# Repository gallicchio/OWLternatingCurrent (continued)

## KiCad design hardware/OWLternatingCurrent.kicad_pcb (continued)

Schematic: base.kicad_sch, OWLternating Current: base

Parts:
AE1: moon; TestPoint_Pad_D1.5mm
AE2: ghost; TestPoint_Pad_D1.5mm
C1: 470u 35V; CP_Elec_10x12.6; MPN MA35V470M10X13; LCSC C46550472
C2, C3, C32, C49, C54, C59, C64, C69, C74: 10u 25V; C_0805_2012Metric; MPN CL21A106KAYNNNE; LCSC C15850
C4, C5, C35, C37, C40, C42, C43, C45, C47, C48, C52, C53, C57, C58, C62, C63, C66, C68, C70, C71, C73, C75: 100n; C_0603_1608Metric; MPN CC0603KRX7R9BB104; LCSC C14663
C6, C7: 22u 25V; C_0805_2012Metric; MPN CL21A226MAQNNNE; LCSC C45783
C8, C9: 1u; C_0402_1005Metric; MPN CL05A105KA5NQNC; LCSC C52923
C10: 4.7u; C_0402_RPi; MPN CL05A475MP5NRNC; LCSC C23733
C11, C12: 4.7u; C_0402_RPi_wide; MPN CL05A475MP5NRNC; LCSC C23733
C13, C14, C15, C16, C17, C18, C19, C20, C21, C22, C23, C24: 100n; C_0402_1005Metric; MPN CL05B104KO5NNNC; LCSC C1525
C25: 10u; C_0603_1608Metric; MPN CL10A106KP8NNNC; LCSC C19702
C26, C27: 15p; C_0402_1005Metric; MPN 0402CG150J500NT; LCSC C1548
C28, C31, C46, C51, C56, C61: 22n; C_0603_1608Metric; MPN CL10B223KB8NNNC; LCSC C21122
C29, C30, C50, C55, C60, C65: 10n; C_0603_1608Metric; MPN 0603B103K500NT; LCSC C57112
C33, C34, C39, C41, C44, C67, C72: 1u; C_0603_1608Metric; MPN CL10A105KB8NNNC; LCSC C15849
C36, C38: 15p; C_0603_1608Metric; MPN CL10C150JB8NNNC; LCSC C1644
D1: BZT52C10; D_SOD-123; MPN BZT52C10; LCSC C173431
D2: SMBJ15A; D_SMB; MPN SMBJ15A; LCSC C19077569
D3, D4: B5819W; D_SOD-123; MPN B5819W SL; LCSC C8598
D5, D6: ESD 0.9pF; D_SOD-923; MPN ESD9L5.0ST5G; LCSC C82326
D7, D8, D32: orange x3; LED_RGB_5050-6; MPN HL-AF-5060S22OC-3-S1-THL; LCSC C516304
D9, D10, D11, D12, D14, D18, D28, D30, D31, D33, D34, D35: purple; LED_0603_1608Metric; MPN GL0603PU01; LCSC C51933300
D13, D15, D16, D17, D19, D20, D21, D22, D23, D24, D25, D26, D27, D29, D36, D37: violet; LED_Everlight-SMD3528_3.5x2.8mm_67-21ST; MPN HL-A-3528S7VC-S1-13HL; LCSC C516136
F1: 3A PTC; Fuse_2920_7451Metric; MPN BSMD2920-300-24V; LCSC C2977527
H1, H2, H3, H4: foot; MountingHole_3.2mm_M3
J1: 12V DC; BarrelJack_XKB_DC-005-5A-2.0_Horizontal; MPN DC-005-5A-2.0; LCSC C381116
J2: USB-C; USB_C_Receptacle_HRO_TYPE-C-31-M-12; MPN TYPE-C-31-M-12; LCSC C165948
J3: TREE; PinSocket_2x08_P2.54mm_Vertical; MPN PM254-2-08-Z-8.5; LCSC C2897409
J4: SWD; JST_SH_BM03B-SRSS-TB_1x03-1MP_P1.00mm_Vertical; MPN BM03B-SRSS-TB(LF)(SN); LCSC C160389
J5: UART; JST_SH_BM03B-SRSS-TB_1x03-1MP_P1.00mm_Vertical; MPN BM03B-SRSS-TB(LF)(SN); LCSC C160389
L1: 10uH; L_Changjiang_FXL0630; MPN FXL0630-100-M; LCSC C167223
L2: 3.3uH; L_Abracon_AOTA-B201610_RPi; MPN AOTA-B201610S3R3-101-T; LCSC C42411119
L3, L4, L5: 33uH coil; Coil_PEND; MPN PCB coil
L6, L7: 30uH coil; Coil_PERCH; MPN PCB coil
LS1: 8R 1W; Speaker_GSPK2307P_D23mm_P10mm; MPN GSPK2307P-8R1W; LCSC C530531
Q1: AO4407A; SOIC-8_3.9x4.9mm_P1.27mm; MPN AO4407A; LCSC C2841482
R1, R2, R22, R25, R28, R47, R52, R56: 100k; R_0603_1608Metric; MPN 0603WAF1003T5E; LCSC C25803
R3, R48: 22k; R_0603_1608Metric; MPN 0603WAF2202T5E; LCSC C31850
R4: 36k; R_0603_1608Metric; MPN 0603WAF3602T5E; LCSC C23147
R5: 5.1k; R_0603_1608Metric; MPN 0603WAF5101T5E; LCSC C23186
R6: 33; R_0402_RPi; MPN 0402WGF330JTCE; LCSC C25105
R7, R8: 27; R_0402_1005Metric; MPN RC0402FR-0727RL; LCSC C138021
R9, R10: 5.1k; R_0402_1005Metric; MPN 0402WGF5101TCE; LCSC C25905
R11, R14: 1k; R_0402_1005Metric; MPN 0402WGF1001TCE; LCSC C11702
R12, R13, R15, R16: 100; R_0402_1005Metric; MPN 0402WGF1000TCE; LCSC C25076
R17, R18, R19, R26, R29, R36, R38, R40, R42, R53, R57: 1k; R_0603_1608Metric; MPN 0603WAF1001T5E; LCSC C21190
R20, R21: 220k; R_0603_1608Metric; MPN 0603WAF2203T5E; LCSC C22961
R23, R34, R43, R44, R45, R46, R51, R55: 10k; R_0603_1608Metric; MPN 0603WAF1002T5E; LCSC C25804
R24, R27: 33; R_0603_1608Metric; MPN 0603WAF330JT5E; LCSC C23140
R30, R31, R35, R37, R39, R41: 2.2k; R_0603_1608Metric; MPN 0603WAF2201T5E; LCSC C4190
R32: 3.3k; R_0603_1608Metric; MPN 0603WAF3301T5E; LCSC C22978
R33, R49: 4.7k; R_0603_1608Metric; MPN 0603WAF4701T5E; LCSC C23162
R50, R54: 0.1; R_1206_3216Metric; MPN 1206W4F100LT5E; LCSC C25334
SW1: BOOT; SW_SPST_TS-1088-xR020; MPN TS-1088-AR02016; LCSC C720477
SW2: SPELL; SW_SPST_TS-1088-xR020; MPN TS-1088-AR02016; LCSC C720477
SW3: SOUND; SW_SPDT_Shouhan_MSK12C02; MPN MSK12C02; LCSC C431540
TP1: +12V; TestPoint_Pad_D1.5mm
TP2: +4.8V; TestPoint_Pad_D1.5mm
TP3: +3V3; TestPoint_Pad_D1.0mm
TP4: VSYS; TestPoint_Pad_D1.0mm
TP5: +1V1; TestPoint_Pad_D1.0mm
TP6: VBUS; TestPoint_Pad_D1.0mm
U1: TPS54302; SOT-23-6; MPN TPS54302DDCR; LCSC C311983
U2: XC6206 3.3V; SOT-23; MPN XC6206P332MR-G; LCSC C5446
U3: LP5036; VQFN-46-1EP_5x6mm_P0.4mm_EP2.8x3.8mm; MPN LP5036RJVR; LCSC C701961
U4: RP2354A; RP2350A_QFN-60_7x7mm_P0.4mm_RPi; MPN RP2354A; LCSC C41378174
U5, U6, U7, U8: DRV8874; HTSSOP-16-1EP_4.4x5mm_P0.65mm_EP3.55x2.46mm_TI_PWP0016J; MPN DRV8874PWPR; LCSC C1855818
U9, U10: UCC27524; SOIC-8_3.9x4.9mm_P1.27mm; MPN UCC27524DR; LCSC C465729
U11: 74HC4051; TSSOP-16_4.4x5mm_P0.65mm; MPN 74HC4051PW,118; LCSC C5645
U12, U13: 74LVC1G14; SOT-23-5; MPN SN74LVC1G14DBVR; LCSC C7835
U14: NS4150B; MSOP-8_3x3mm_P0.65mm; MPN NS4150B; LCSC C189961
U15: LSM6DS3TR-C; Bosch_LGA-14_3x2.5mm_P0.5mm; MPN LSM6DS3TR-C; LCSC C967633
U16: LTR-303ALS; Lite-On_LTR-303ALS-01; MPN LTR-303ALS-01; LCSC C364577
U17: TMAG5273A2; SOT-23-6; MPN TMAG5273A2QDBVR; LCSC C3715882
U18: OPA2333; SOIC-8_3.9x4.9mm_P1.27mm; MPN OPA2333AIDR; LCSC C38732
Y1: 12MHz; Crystal_SMD_3225-4Pin_3.2x2.5mm; MPN ABM8-272-T3; LCSC C20625731

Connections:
+1V1: C12.1, C13.1, C14.1, C15.1, L2.1, TP5.1, U4.6 (DVDD), U4.23 (DVDD), U4.39 (DVDD), U4.50 (VREG_FB)
+3V3: C9.1, C11.1, C16.1, C17.1, C18.1, C19.1, C20.1, C21.1, C22.1, C23.1, C24.1, C35.1, C37.1, C39.1, C40.1, C42.1, C43.1, C44.1, C45.1, C66.1, C71.1, J3.2, R6.1, R30.1, R31.1, R34.1, TP3.1, U2.2 (VO), U3.40 (VCC), U3.43 (EN), U4.1 (IOVDD), U4.11 (IOVDD), U4.20 (IOVDD), U4.30 (IOVDD), U4.38 (IOVDD), U4.44 (ADC_AVDD), U4.45 (IOVDD), U4.49 (VREG_VIN), U4.53 (USB_OTP_VDD), U4.54 (QSPI_IOVDD), U5.5 (VREF), U5.16 (PMODE), U6.5 (VREF), U6.16 (PMODE), U7.5 (VREF), U7.16 (PMODE), U8.5 (VREF), U8.16 (PMODE), U11.16 (VCC), U12.5 (VCC), U13.5 (VCC), U15.5 (VDDIO), U15.8 (VDD), U15.12 (CS), U16.1 (VDD), U17.4 (VCC), U18.8 (V+)
+5V: C6.1, C7.1, C32.1, C33.1, C67.1, C68.1, C72.1, C73.1, D3.2 (A), D7.1 (A), D7.2 (A), D7.3 (A), D8.1 (A), D8.2 (A), D8.3 (A), D9.2 (A), D10.2 (A), D11.2 (A), D12.2 (A), D13.2 (A), D14.2 (A), D15.2 (A), D16.2 (A), D17.2 (A), D18.2 (A), D19.2 (A), D20.2 (A), D21.2 (A), D22.2 (A), D23.2 (A), D24.2 (A), D25.2 (A), D26.2 (A), D27.2 (A), D28.2 (A), D29.2 (A), D30.2 (A), D31.2 (A), D32.1 (A), D32.2 (A), D32.3 (A), D33.2 (A), D34.2 (A), D35.2 (A), D36.2 (A), D37.2 (A), J3.4, L1.2, R4.1, R45.1, SW3.1 (A), TP2.1, U9.6 (VDD), U10.6 (VDD), U14.6 (VCC)
+12V: C1.1, C2.1, C3.1, C4.1, C47.2, C48.1, C49.1, C52.2, C53.1, C54.1, C57.2, C58.1, C59.1, C62.2, C63.1, C64.1, D1.1 (K), D2.1 (K), Q1.1 (S), Q1.2 (S), Q1.3 (S), R2.1, R47.1, TP1.1, U1.3 (VIN), U5.11 (VM), U6.11 (VM), U7.11 (VM), U8.11 (VM)
/Base/AUDIO: R18.2, U4.12 (GPIO8)
/Base/BUTTON: R17.2, U4.29 (GPIO18)
/Base/CATRING0: D34.1 (K), U3.33 (OUT32)
/Base/CATRING1: D35.1 (K), U3.34 (OUT33)
/Base/CATRING2: D28.1 (K), U3.27 (OUT26)
/Base/CAT_A: C74.1, U10.7 (OUTA)
/Base/CAT_B: L7.2, U10.5 (OUTB)
/Base/CAT_C: C74.2, L7.1
/Base/DRV_nFAULT: R34.2, U4.34 (GPIO22), U5.4 (~FAULT), U6.4 (~FAULT), U7.4 (~FAULT), U8.4 (~FAULT)
/Base/DRV_nSLEEP: R33.1, U4.31 (GPIO19), U5.3 (~SLEEP), U6.3 (~SLEEP), U7.3 (~SLEEP), U8.3 (~SLEEP)
/Base/FAM1_A: U4.7 (GPIO4), U9.2 (INA)
/Base/FAM1_B: U4.8 (GPIO5), U9.4 (INB)
/Base/FAM1_IAVG: C70.1, R51.2, U18.3 (+)
/Base/FAM1_ISENSE: R52.2, U11.13 (A0), U18.1
/Base/FAM2_A: U4.18 (GPIO14), U10.2 (INA)
/Base/FAM2_B: U4.19 (GPIO15), U10.4 (INB)
/Base/FAM2_IAVG: C75.1, R55.2, U18.5 (+)
/Base/FAM2_ISENSE: R56.2, U11.12 (A3), U18.7
/Base/FAM_EN: R49.1, U4.35 (GPIO23), U9.1 (ENA), U9.8 (ENB), U10.1 (ENA), U10.8 (ENB)
/Base/GHOST: AE2.1, D6.1 (K), R29.1
/Base/HALL: J3.1, U4.41 (GPIO27/ADC1)
/Base/IMU_INT: U4.3 (GPIO1), U15.4 (INT1)
/Base/LEV_A: J3.14, J3.16, U8.8 (OUT1)
/Base/LEV_B: J3.8, J3.10, U8.10 (OUT2)
/Base/LEV_IN1: U4.16 (GPIO12), U8.1 (IN1)
/Base/LEV_IN2: U4.17 (GPIO13), U8.2 (IN2)
/Base/LEV_IPROPI: C50.1, R36.2, U4.42 (GPIO28/ADC2)
/Base/MOON: AE1.1, D5.1 (K), R26.1
/Base/MUX_OUT: U4.43 (GPIO29/ADC3), U11.3 (A)
/Base/MUX_S0: U4.36 (GPIO24), U11.11 (S0)
/Base/MUX_S1: U4.37 (GPIO25), U11.10 (S1)
/Base/MUX_S2: U4.40 (GPIO26/ADC0), U11.9 (S2)
/Base/OWLRING0: D12.1 (K), U3.6 (OUT5)
/Base/OWLRING1: D18.1 (K), U3.12 (OUT11)
/Base/OWLRING2: D14.1 (K), U3.8 (OUT7)
/Base/OWL_A: C69.1, U9.7 (OUTA)
/Base/OWL_B: L6.2, U9.5 (OUTB)
/Base/OWL_C: C69.2, L6.1
/Base/PEND1_A: L3.1, U5.8 (OUT1)
/Base/PEND1_B: L3.2, U5.10 (OUT2)
/Base/PEND1_IN1: U4.9 (GPIO6), U5.1 (IN1)
/Base/PEND1_IN2: U4.10 (GPIO7), U5.2 (IN2)
/Base/PEND1_IPROPI: C55.1, R38.2, U11.4 (A7)
/Base/PEND2_A: L4.1, U6.8 (OUT1)
/Base/PEND2_B: L4.2, U6.10 (OUT2)
/Base/PEND2_IN1: U4.4 (GPIO2), U6.1 (IN1)
/Base/PEND2_IN2: U4.5 (GPIO3), U6.2 (IN2)
/Base/PEND2_IPROPI: C60.1, R40.2, U11.5 (A5)
/Base/PEND3_A: L5.1, U7.8 (OUT1)
/Base/PEND3_B: L5.2, U7.10 (OUT2)
/Base/PEND3_IN1: U4.14 (GPIO10), U7.1 (IN1)
/Base/PEND3_IN2: U4.15 (GPIO11), U7.2 (IN2)
/Base/PEND3_IPROPI: C65.1, R42.2, U11.15 (A2)
/Base/PUMPKIN0: D8.4 (K), D8.5 (K), D8.6 (K), U3.2 (OUT1)
/Base/PUMPKIN1: D7.4 (K), D7.5 (K), D7.6 (K), U3.1 (OUT0)
/Base/PUMPKIN2: D32.4 (K), D32.5 (K), D32.6 (K), U3.31 (OUT30)
/Base/QSPI_SS: R14.2, U4.60 (~QSPI_SS)
/Base/SCL: J3.5, R30.2, U3.42 (SCL), U4.33 (GPIO21), U15.13 (SCL), U16.4 (SCL), U17.1 (SCL)
/Base/SDA: J3.3, R31.2, U3.41 (SDA), U4.32 (GPIO20), U15.14 (SDA), U16.6 (SDA), U17.6 (SDA)
/Base/STAR0: D17.1 (K), U3.11 (OUT10)
/Base/STAR1: D16.1 (K), U3.10 (OUT9)
/Base/STAR2: D15.1 (K), U3.9 (OUT8)
/Base/STAR3: D13.1 (K), U3.7 (OUT6)
/Base/STAR4: D37.1 (K), U3.36 (OUT35)
/Base/STAR5: D36.1 (K), U3.35 (OUT34)
/Base/STAR6: D29.1 (K), U3.28 (OUT27)
/Base/STAR7: D24.1 (K), U3.23 (OUT22)
/Base/STAR8: D23.1 (K), U3.22 (OUT21)
/Base/STAR9: D25.1 (K), U3.24 (OUT23)
/Base/STAR10: D26.1 (K), U3.25 (OUT24)
/Base/STAR11: D27.1 (K), U3.26 (OUT25)
/Base/STARX0: D20.1 (K), U3.14 (OUT13)
/Base/STARX1: D21.1 (K), U3.20 (OUT19)
/Base/STARX2: D19.1 (K), U3.13 (OUT12)
/Base/STARX3: D22.1 (K), U3.21 (OUT20)
/Base/SWCLK: R12.2, U4.24 (SWCLK)
/Base/SWDIO: R13.2, U4.25 (SWDIO)
/Base/THEREMIN_PITCH: R24.2, U4.2 (GPIO0)
/Base/THEREMIN_VOL: R27.2, U4.13 (GPIO9)
/Base/UART_RX: R15.2, U4.28 (GPIO17)
/Base/UART_TX: R16.2, U4.27 (GPIO16)
/Base/USB_D+: J2.A6 (D+), J2.B6 (D+), R8.1
/Base/USB_D-: J2.A7 (D-), J2.B7 (D-), R7.1
/Base/USB_DM: R7.2, U4.51 (USB_DM)
/Base/USB_DP: R8.2, U4.52 (USB_DP)
/Base/V5_SENSE: R45.2, R46.1, U11.1 (A4)
/Base/V12_SENSE: R47.2, R48.1, U11.2 (A6)
/Base/VBUS_SENSE: R43.2, R44.1, U11.14 (A1)
/Base/WISP0: D10.1 (K), U3.4 (OUT3)
/Base/WISP1: D9.1 (K), U3.3 (OUT2)
/Base/WISP2: D11.1 (K), U3.5 (OUT4)
/Base/WISP3: D33.1 (K), U3.32 (OUT31)
/Base/WISP4: D31.1 (K), U3.30 (OUT29)
/Base/WISP5: D30.1 (K), U3.29 (OUT28)
/Base/XIN: C26.2, U4.21 (XIN), Y1.1
/Base/XOUT: R11.2, U4.22 (XOUT)
GND: C1.2, C2.2, C3.2, C4.2, C6.2, C7.2, C8.2, C9.2, C10.2, C11.2, C12.2, C13.2, C14.2, C15.2, C16.2, C17.2, C18.2, C19.2, C20.2, C21.2, C22.2, C23.2, C24.2, C25.2, C26.1, C27.1, C29.2, C30.2, C31.2, C32.2, C33.2, C34.2, C35.2, C36.2, C37.2, C38.2, C39.2, C40.2, C41.2, C42.2, C43.2, C44.2, C45.2, C48.2, C49.2, C50.2, C53.2, C54.2, C55.2, C58.2, C59.2, C60.2, C63.2, C64.2, C65.2, C66.2, C67.2, C68.2, C70.2, C71.2, C72.2, C73.2, C75.2, D2.2 (A), D5.2 (A), D6.2 (A), J1.2, J1.3, J2.A1 (GND), J2.A12 (GND), J2.B1 (GND), J2.B12 (GND), J2.SH (SHIELD), J3.6, J3.7, J3.9, J3.11, J3.12, J3.13, J3.15, J4.2 (GND), J4.MP, J5.2 (GND), J5.MP, R1.2, R3.2, R5.2, R9.2, R10.2, R22.2, R32.2, R33.2, R35.2, R37.2, R39.2, R41.2, R44.2, R46.2, R48.2, R49.2, R50.2, R53.2, R54.2, R57.2, SW1.1, SW2.1, SW3.3 (C), U1.1 (GND), U2.1 (GND), U3.37 (GND), U3.38 (ADDR0), U3.39 (ADDR1), U3.46 (GND), U3.47 (GND), U4.47 (VREG_PGND), U4.61 (GND), U5.7 (IMODE), U5.9 (PGND), U5.15 (GND), U5.17 (PAD), U6.7 (IMODE), U6.9 (PGND), U6.15 (GND), U6.17 (PAD), U7.7 (IMODE), U7.9 (PGND), U7.15 (GND), U7.17 (PAD), U8.7 (IMODE), U8.9 (PGND), U8.15 (GND), U8.17 (PAD), U11.6 (~E), U11.7 (VEE), U11.8 (GND), U12.3 (GND), U13.3 (GND), U14.7 (GND), U15.1 (SDO/SA0), U15.2 (SDx), U15.3 (SCx), U15.6 (GND), U15.7 (GND), U16.3 (GND), U17.2 (GND), U17.3 (TEST), U18.4 (V-), Y1.2 (G), Y1.4 (G)
unnamed: C27.2, R11.1, Y1.3
unnamed: C28.1, R20.2
unnamed: C28.2, C30.1, R19.1
unnamed: C29.1, R18.1, R19.2
unnamed: C31.1, R21.2
unnamed: C36.1, R25.1, R26.2, U12.2
unnamed: C38.1, R28.1, R29.2, U13.2
unnamed: D1.2 (A), Q1.4 (G), R1.1
unnamed: F1.1, J1.1
unnamed: F1.2, Q1.5 (D), Q1.6 (D), Q1.7 (D), Q1.8 (D)
unnamed: J2.A5 (CC1), R10.1
unnamed: J2.B5 (CC2), R9.1
unnamed: J4.1 (SWCLK), R12.1
unnamed: J4.3 (SWDIO), R13.1
unnamed: J5.1 (RX), R15.1
unnamed: J5.3 (TX), R16.1
unnamed: R14.1, SW1.2
unnamed: R17.1, SW2.2
unnamed: R24.1, R25.2, U12.4
unnamed: R27.1, R28.2, U13.4
unnamed: R23.2, SW3.2 (B)
unnamed: C5.1, U1.6 (BOOT)
unnamed: R2.2, R3.1, U1.5 (EN)
unnamed: R4.2, R5.1, U1.4 (FB)
unnamed: C5.2, L1.1, U1.2 (SW)
unnamed: R32.1, U3.44 (IREF)
unnamed: C41.1, U3.45 (VCAP)
unnamed: C10.1, R6.2, U4.46 (VREG_AVDD)
unnamed: L2.2, U4.48 (VREG_LX)
unnamed: C51.1, U5.13 (CPH)
unnamed: C51.2, U5.14 (CPL)
unnamed: R37.1, R38.1, U5.6 (IPROPI)
unnamed: C52.1, U5.12 (VCP)
unnamed: C56.1, U6.13 (CPH)
unnamed: C56.2, U6.14 (CPL)
unnamed: R39.1, R40.1, U6.6 (IPROPI)
unnamed: C57.1, U6.12 (VCP)
unnamed: C61.1, U7.13 (CPH)
unnamed: C61.2, U7.14 (CPL)
unnamed: R41.1, R42.1, U7.6 (IPROPI)
unnamed: C62.1, U7.12 (VCP)
unnamed: C46.1, U8.13 (CPH)
unnamed: C46.2, U8.14 (CPL)
unnamed: R35.1, R36.1, U8.6 (IPROPI)
unnamed: C47.1, U8.12 (VCP)
unnamed: R50.1, R51.1, U9.3 (GND)
unnamed: R54.1, R55.1, U10.3 (GND)
unnamed: C34.1, U14.2 (BYPASS)
unnamed: R22.1, R23.1, U14.1 (CTRL)
unnamed: R21.1, U14.4 (INN)
unnamed: R20.1, U14.3 (INP)
unnamed: LS1.2, U14.5 (VON)
unnamed: LS1.1, U14.8 (VOP)
unnamed: R52.1, R53.1, U18.2 (-)
unnamed: R56.1, R57.1, U18.6 (-)
VBUS: C25.1, D4.2 (A), J2.A4 (VBUS), J2.A9 (VBUS), J2.B4 (VBUS), J2.B9 (VBUS), R43.1, TP6.1
VSYS: C8.1, D3.1 (K), D4.1 (K), TP4.1, U2.3 (VI)

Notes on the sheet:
OWLternating Current: the base board
12 V IN
12 V, 3-5 A adapter (5.5 x 2.1 mm plug, centre positive; ORDER_LIST.md). F1 resets itself after a short: it holds 3 A and trips by 6 A, which a 3-5 A brick can deliver (the board draws 1.5 A at most on average), and it is rated 24 V, the TVS's clamp. Q1 conducts only when the plug is the right way 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
4.8 V BUCK
U1, TPS54302: 12 V to 4.8 V, 3 A, 400 kHz. 4.8 V, not 5: 0.596 V x (1 + 36k/5.1k) = 4.80 V from a Preferred and a Basic resistor, and it keeps the audio amplifier (5.25 V absolute maximum) clear of its limit. The rail is called +5V; it runs the LEDs, the perch drivers, the audio amplifier and the t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
VSYS AND 3.3 V
VSYS is 4.8 V less a Schottky drop, or USB's 5 V less one: so the RP2354A, the sensors and the LED drivers' logic run from USB alone (to program the board without the adapter), while USB never feeds the 4.8 V rail and its loads. U2, XC6206: 3.3 V, 200 mA, stable with ceramic capacitors; the logic d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
Core regulator (1.1 V): Raspberry Pi's parts and layout, copied exactly (gen/rpi_minimal), as on GPiBridge. L2 is polarity-marked: its dot must sit as their footprint shows.
3.3 V and 1.1 V: one 100 nF at every supply pin. ADC_AVDD shares the 3.3 V: the ADC reads currents and a Hall sensor to 1 %, not microvolts.
USB 2.0 full speed, 12 Mbit/s. 27 R at the chip (RP2350 datasheet).
CC1, CC2: 5.1 k to ground say 'device'; the host then gives 5 V.
USB-C: programming and the console. It powers the logic (about 110 mA), never the LEDs or coils.
ABM8-272-T3, 12 MHz, 10 pF load: the crystal Raspberry Pi specifies, with their 15 pF loads and the 1 k that limits its drive.
Raspberry Pi debug connector (JST- SH 3-pin): the Debug Probe's 'D' cable. 100 R in each line, at the connector. 3.3 V logic.
BOOT: hold it while plugging in to start the RP2354A's USB bootloader. Rarely needed: 'picotool reboot -f -u' gets there from software. RUN stays open: it has its own pull-up inside the RP2354A, and the Debug Probe resets the chip over SWD.
The 2 MB flash is inside the RP2354A; these stay open.
UART0 console, 115200 baud: the Debug Probe's 'U' cable. Works when USB does not.
AUDIO
AUDIO is PWM at about 150 kHz. Two RC stages (1k, 10n: 16 kHz each) leave the tone and take the carrier down 38 dB; 22n and 220k pass 33 Hz and up. U14, NS4150B: class D, gain 240k/220k = 1.1. Full scale is about 0.2 W in the 8 ohm, 23 mm speaker (78 dB at a metre), a bedroom's worth and under a to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
THEREMIN
Each oscillator: a 74LVC1G14 with 100k feedback; its capacitor is 15 pF plus a gold copper shape (the moon, the ghost: their pads AE1 and AE2), about 500 kHz. A hand 10 cm away adds a fraction of a picofarad and lowers the frequency by a few kHz; the RP2354A's PIO counts each for 10 ms (100 Hz reso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
I2C at 400 kHz, 3.3 V, 2.2k pull-ups; on it: U3 (LP5036, 0x30), the tree's LP5036 (0x32, through the socket), U15 (LSM6DS3TR-C, 0x6A: taps and tilt), U16 (LTR-303, 0x29: the owls wake at dusk), U17 (TMAG5273A2, 0x35: times the pendulum's kicks). Interrupts the firmware does not use stay open.
U3, LP5036: 36 current sinks, 12-bit PWM at 29 kHz (no flicker a camera or an eye can see), in 12 banks of 3 that share a brightness. R3K3 on IREF sets the most any output can sink: 105 x 0.7 V / 3.3k = 22 mA, under every LED's 30 mA, whatever the firmware asks. The LEDs' anodes are on 4.8 V; the n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
U8, U5-U7: DRV8874 H-bridges from 12 V. PMODE high: PWM mode (IN1 and IN2 drive the bridge; both low: coast). IMODE to ground: fixed off-time chopping at ITRIP = 3.3 V / (450 uA/A x 2.2k) = 3.3 A, so no coil ever carries more. IPROPI mirrors the low-side current, 450 uA per amp: 2.2k makes 1 V per 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
U8 drives the levitation coil on the perch (LEV_A, LEV_B: up the right edge to the tree's socket). L3-L5: the pendulum coils under the bat's swing, about 12 turns on each of 4 layers, 33 uH, 2.3 ohm (copper on this board, gen/coils.py).
J3: the tree stands here (its right-angle header). Pins 8, 10: LEV_B; 14, 16: LEV_A (3.3 A at most, two pins each); 1 HALL; 3 SDA; 5 SCL; 2 3.3 V; 4 4.8 V; the rest ground, between the coil's pins and the signals.
H1-H4: 3.2 mm holes at the corners; the printed feet snap into them.

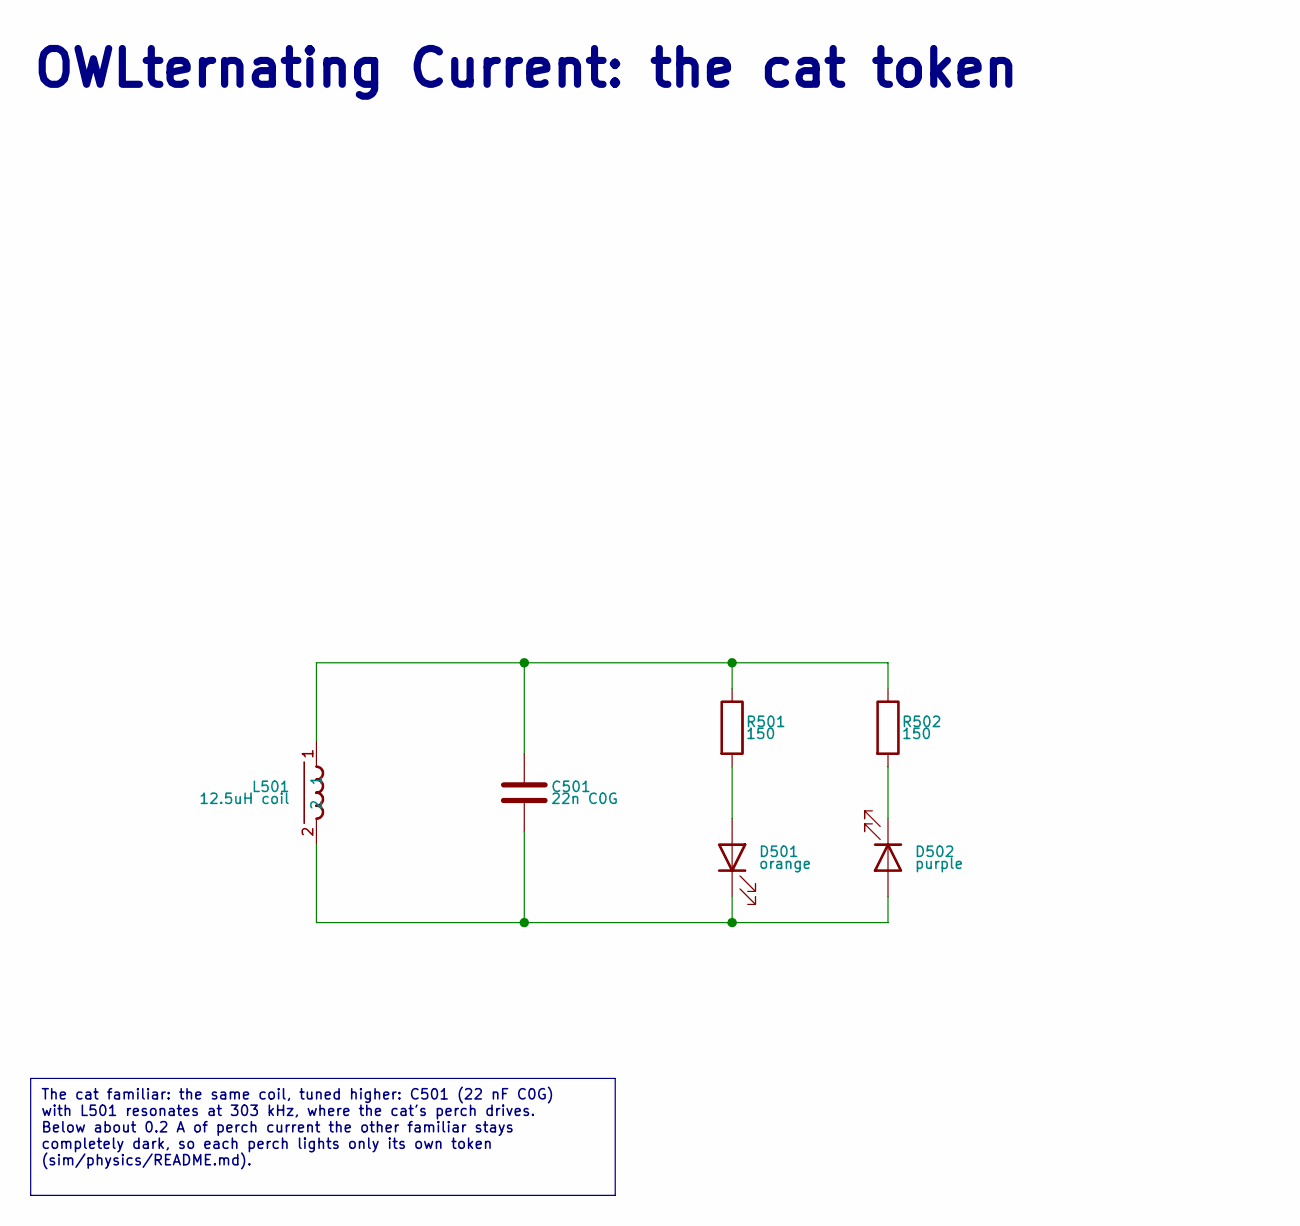
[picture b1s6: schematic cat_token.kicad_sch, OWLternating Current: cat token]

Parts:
C501: 22n C0G; C_0805_2012Metric; MPN GRM21B5C1H223JA01L; LCSC C77069
D501: orange; LED_0603_1608Metric; MPN XL-1608UOC-06; LCSC C965800
D502: purple; LED_0603_1608Metric; MPN GL0603PU01; LCSC C51933300
L501: 12.5uH coil; Coil_TOKEN; MPN PCB coil
R501, R502: 150; R_0603_1608Metric; MPN 0603WAF1500T5E; LCSC C22808

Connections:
unnamed: C501.1, L501.1, R501.1, R502.1
unnamed: D501.2 (A), R501.2
unnamed: C501.2, D501.1 (K), D502.2 (A), L501.2
unnamed: D502.1 (K), R502.2

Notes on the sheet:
OWLternating Current: the cat token
The cat familiar: the same coil, tuned higher: C501 (22 nF C0G) with L501 resonates at 303 kHz, where the cat's perch drives. Below about 0.2 A of perch current the other familiar stays completely dark, so each perch lights only its own token (sim/physics/README.md).

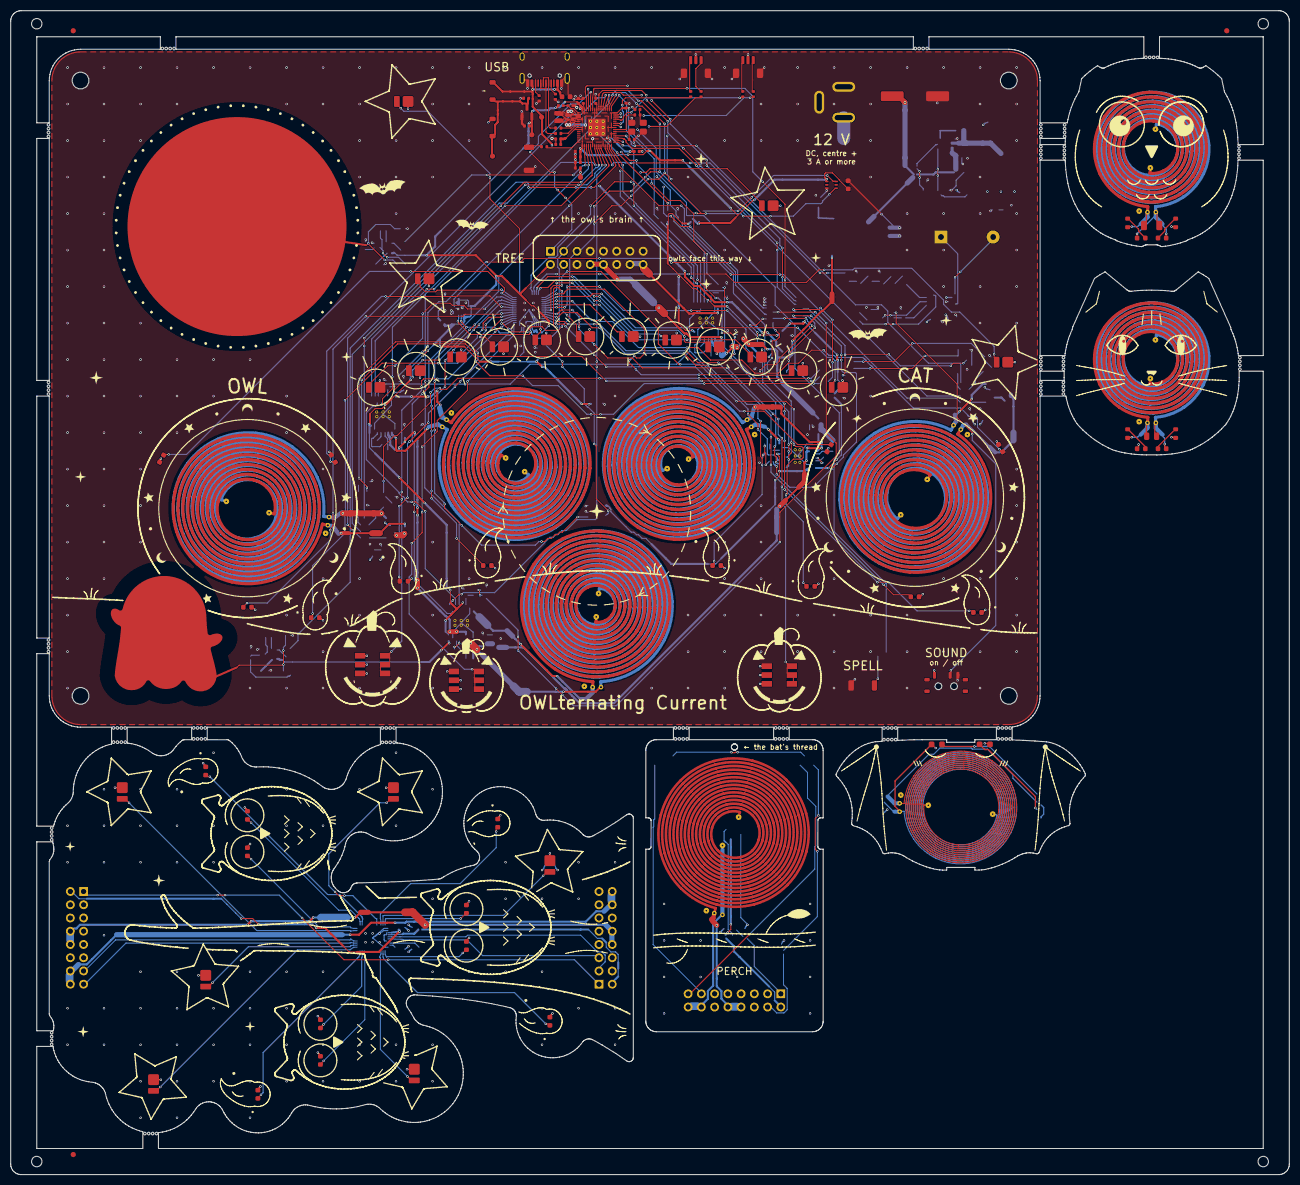
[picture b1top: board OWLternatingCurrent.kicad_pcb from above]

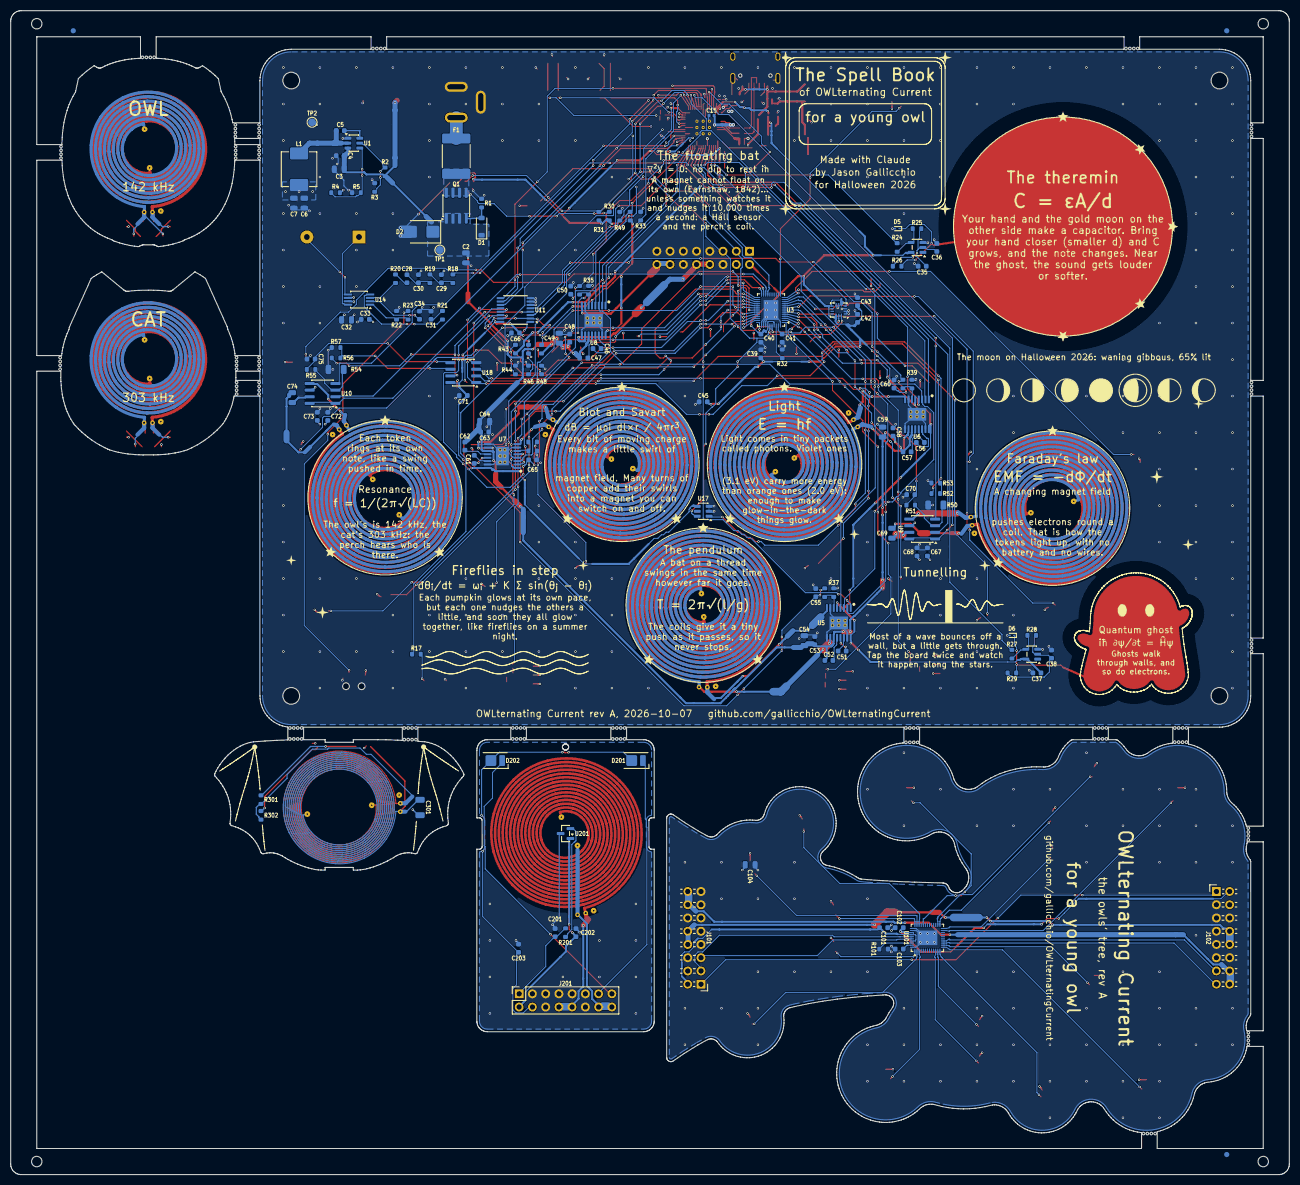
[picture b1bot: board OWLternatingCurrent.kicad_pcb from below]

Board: 4 copper layers, 245.2 x 223.2 mm, 408 parts (143 on the bottom side), 207 nets.

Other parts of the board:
FID1, FID2, FID3: Fiducial_1mm_Mask2mm
MB1, MB2, MB3, MB4, MB5, MB6, MB7, MB8, MB9, MB10, MB11, MB12, MB13, MB14, MB15, MB16, MB17, MB18, MB19, MB20, MB21, MB22, MB23, MB24, MB25, MB26, MB27, MB28, MB29, MB30, MB31, MB32, MB33, MB34, MB35, MB36, MB37, MB38, MB39, MB40, MB41, MB42, MB43, MB44, MB45, MB46, MB47, MB48, MB49, MB50, MB51, MB52, MB53, MB54, MB55, MB56, MB57, MB58, MB59, MB60, MB61, MB62, MB63, MB64, MB65, MB66, MB67, MB68, MB69, MB70, MB71, MB72, MB73, MB74, MB75, MB76, MB77, MB78, MB79, MB80, MB81, MB82, MB83, MB84, MB85, MB86, MB87, MB88, MB89, MB90, MB91, MB92, MB93, MB94, MB95, MB96, MB97, MB98, MB99, MB100, MB101, MB102, MB103, MB104, MB105, MB106, MB107, MB108, MB109, MB110, MB111, MB112, MB113, MB114, MB115, MB116, MB117, MB118, MB119, MB120, MB121, MB122, MB123, MB124, MB125, MB126, MB127, MB128, MB129, MB130, MB131, MB132: MouseBite_NPTH_0.5mm
TH1, TH2, TH3, TH4: Tooling_NPTH_2mm

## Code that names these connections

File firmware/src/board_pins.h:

/* board_pins.h: which RP2354A GPIO does what on OWLternating Current rev A.
 * WRITTEN BY gen/firmware_pins.py FROM gen/pins.py: edit that, not this. */
#pragma once

/* ---- every GPIO ---------------------------------------------------------- */
#define PIN_THEREMIN_PITCH    0   /* in: pitch oscillator (moon antenna), counted by PIO */
#define PIN_IMU_INT           1   /* in: LSM6DS3TR-C INT1: taps, tilt, free fall */
#define PIN_PEND2_IN1         2   /* out: pendulum coil 2 bridge (U6) IN1; PWM1 A */
#define PIN_PEND2_IN2         3   /* out: pendulum coil 2 bridge IN2; PWM1 B */
#define PIN_FAM1_A            4   /* out: owl perch bridge, leg A (UCC27524 U9, channel A); PWM2 A */
#define PIN_FAM1_B            5   /* out: owl perch bridge, leg B (U9, channel B); PWM2 B */
#define PIN_PEND1_IN1         6   /* out: pendulum coil 1 bridge (DRV8874 U5) IN1; PWM3 A */
#define PIN_PEND1_IN2         7   /* out: pendulum coil 1 bridge IN2; PWM3 B */
#define PIN_AUDIO             8   /* out: audio PWM to the class-D amplifier through an RC filter; PWM4 A */
#define PIN_THEREMIN_VOL      9   /* in: volume oscillator (pumpkin antenna), counted by PIO */
#define PIN_PEND3_IN1        10   /* out: pendulum coil 3 bridge (U7) IN1; PWM5 A */
#define PIN_PEND3_IN2        11   /* out: pendulum coil 3 bridge IN2; PWM5 B */
#define PIN_LEV_IN1          12   /* out: levitation coil bridge (U8) IN1; PWM6 A */
#define PIN_LEV_IN2          13   /* out: levitation coil bridge IN2; PWM6 B */
#define PIN_FAM2_A           14   /* out: cat perch bridge, leg A (UCC27524 U10, channel A); PWM7 A */
#define PIN_FAM2_B           15   /* out: cat perch bridge, leg B (U10, channel B); PWM7 B */
#define PIN_UART_TX          16   /* out: UART0 TX to the debug connector J5 (console, 115200) */
#define PIN_UART_RX          17   /* in: UART0 RX from J5 */
#define PIN_BUTTON           18   /* in: the SPELL button, low when pressed (internal pull-up: RP2350-E9 affects only pull-downs) */
#define PIN_DRV_nSLEEP       19   /* out: all four DRV8874s: low = asleep (4.7 k pull-down keeps them asleep in reset) */
#define PIN_SDA              20   /* io: I2C0 SDA: LED drivers, IMU, light sensor, 3-axis Hall; the tree's LED driver */
#define PIN_SCL              21   /* out: I2C0 SCL */
#define PIN_DRV_nFAULT       22   /* in: all four DRV8874s' nFAULT, wired-OR, 10 k pull-up */
#define PIN_FAM_EN           23   /* out: both UCC27524s' four enables (4.7 k pull-down beats their internal pull-ups: off in reset) */
#define PIN_MUX_S0           24   /* out: 74HC4051 select bit 0 */
#define PIN_MUX_S1           25   /* out: 74HC4051 select bit 1 */
#define PIN_MUX_S2           26   /* out: 74HC4051 select bit 2 */
#define PIN_HALL             27   /* adc: ADC1: the perch's DRV5055 Hall sensor (via the tree) */
#define PIN_LEV_IPROPI       28   /* adc: ADC2: levitation coil current (DRV8874 IPROPI) */
#define PIN_MUX_OUT          29   /* adc: ADC3: the 74HC4051's output (slow signals, below) */

/* ---- the coil bridges: one PWM slice each, IN1/leg A = channel A -------------- */
#define PWM_SLICE_PEND1  3   /* GPIO6 (IN1) = A, GPIO7 (IN2) = B */
#define PWM_SLICE_PEND2  1   /* GPIO2 (IN1) = A, GPIO3 (IN2) = B */
#define PWM_SLICE_PEND3  5   /* GPIO10 (IN1) = A, GPIO11 (IN2) = B */
#define PWM_SLICE_LEV    6   /* GPIO12 (IN1) = A, GPIO13 (IN2) = B */
#define PWM_SLICE_FAM1   2   /* GPIO4 (leg A) = A, GPIO5 (leg B) = B */
#define PWM_SLICE_FAM2   7   /* GPIO14 (leg A) = A, GPIO15 (leg B) = B */
#define PWM_SLICE_AUDIO  4   /* GPIO8 = A */
#define PWM_SLICE_TICK   0   /* no PWM output: GPIO0 and GPIO1 carry THEREMIN_PITCH and IMU_INT */

/* ---- the ADC inputs ---------------------------------------------------- */
#define ADC_CH_HALL         1   /* GPIO27 */
#define ADC_CH_LEV_IPROPI   2   /* GPIO28 */
#define ADC_CH_MUX_OUT      3   /* GPIO29 */
/* the round robin (from ADC_RR_FIRST, ascending): a burst's samples in this order */
#define ADC_RR_MASK      0xeu
#define ADC_RR_FIRST     1
#define ADC_SLOT_HALL       0   /* ADC1 */
#define ADC_SLOT_LEV_IPROPI 1   /* ADC2 */
#define ADC_SLOT_MUX_OUT    2   /* ADC3 */

/* ---- the 74HC4051 (S0-S2 on PIN_MUX_S0..S2) ------------------------------ */
#define MUX_SEL_SHIFT    24
#define MUX_SEL_MASK     (7u << MUX_SEL_SHIFT)
#define MUX_CH_FAM1_ISENSE    0   /* owl perch bridge's supply current, 1 ms average, x20.6 on 0.5 R: 10.3 V/A; rises when the owl sits on it */
#define MUX_CH_VBUS_SENSE     1   /* USB VBUS through 10 k / 10 k: plugged into USB? */
#define MUX_CH_PEND3_IPROPI   2   /* pendulum coil 3 current */
#define MUX_CH_FAM2_ISENSE    3   /* cat perch bridge's supply current, 1 ms average, x20.6 on 0.5 R: 10.3 V/A; rises when the cat sits on it */
#define MUX_CH_V5_SENSE       4   /* +5V through 10 k / 10 k (5 V reads 2.5 V) */
#define MUX_CH_PEND2_IPROPI   5   /* pendulum coil 2 current */
#define MUX_CH_V12_SENSE      6   /* +12V through 100 k / 22 k (12 V reads 2.16 V) */
#define MUX_CH_PEND1_IPROPI   7   /* pendulum coil 1 current */
#define MUX_CHANNELS     8
#define VBUS_DIVIDER         0.500000f   /* sense voltage / rail: 10 k over 10 k */
#define V5_DIVIDER           0.500000f   /* sense voltage / rail: 10 k over 10 k */
#define V12_DIVIDER          0.180328f   /* sense voltage / rail: 100 k over 22 k */

/* ---- I2C0 (7-bit addresses) ------------------------------------------------- */
#define I2C_ADDR_LP5036_BASE  0x30
#define I2C_ADDR_LP5036_TREE  0x32
#define I2C_ADDR_LSM6DS3TR_C  0x6A
#define I2C_ADDR_LTR_303ALS   0x29
#define I2C_ADDR_TMAG5273A2   0x35

/* ---- what the board's own resistors hold while the RP2354A is in reset ---- */
#define BOARD_PULL_UP_MASK    ((1u << PIN_DRV_nFAULT))
#define BOARD_PULL_DOWN_MASK  ((1u << PIN_DRV_nSLEEP) | (1u << PIN_FAM_EN))
/* the pins that rely on the pad's own pull-up (pull-ups are not hit by RP2350-E9) */
#define MCU_PULL_UP_MASK      ((1u << PIN_BUTTON))

/* every pin that drives a coil bridge: low = off (DRV8874 coast, UCC27524 output low) */
#define BRIDGE_PIN_MASK  ((1u << PIN_PEND1_IN1) | \
                          (1u << PIN_PEND2_IN1) | \
                          (1u << PIN_PEND3_IN1) | \
                          (1u << PIN_LEV_IN1) | \
                          (1u << PIN_PEND1_IN2) | \
                          (1u << PIN_PEND2_IN2) | \
                          (1u << PIN_PEND3_IN2) | \
                          (1u << PIN_LEV_IN2) | \
                          (1u << PIN_FAM1_A) | \
                          (1u << PIN_FAM2_A) | \
                          (1u << PIN_FAM1_B) | \
                          (1u << PIN_FAM2_B))

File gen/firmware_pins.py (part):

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  * each bridge's PWM slice, checked: IN1 / leg A on the slice's A output,
    IN2 / leg B on its B output (RP2350: GPIO n is slice (n >> 1) & 7,
    channel n & 1);
  * the ADC inputs (GPIO26-29 are ADC0-3 on the QFN-60);
  * the 74HC4051's channels, and the sense dividers' ratios, read from the
    descriptions ("through 100 k / 22 k");
  * the I2C addresses;
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
BRIDGES_DRV = ("PEND1", "PEND2", "PEND3", "LEV")      # DRV8874s: IN1 = A, IN2 = B
BRIDGES_FAM = ("FAM1", "FAM2")                        # UCC27524 legs: A, B
ADC_FIRST_GPIO = 26                                   # QFN-60: GPIO26-29 = ADC0-3


def slice_of(gpio):
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        a, bb = g[b + "_IN1"], g[b + "_IN2"]
        assert slice_of(a) == slice_of(bb), "%s: IN1 and IN2 on different PWM slices" % b
        assert chan_of(a) == 0 and chan_of(bb) == 1, "%s: IN1 must be channel A, IN2 channel B" % b
        assert a < 16, "%s: GPIO16 and up share slices 0-6 with GPIO0-13" % b
        L.append("#define PWM_SLICE_%-6s %d   /* GPIO%d (IN1) = A, GPIO%d (IN2) = B */" % (b, slice_of(a), a, bb))
    for b in BRIDGES_FAM:
        a, bb = g[b + "_A"], g[b + "_B"]
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        L.append("#define ADC_CH_%-12s %d   /* GPIO%d */" % (net, n - ADC_FIRST_GPIO, n))
    # the round robin converts the enabled channels in ascending order from the one
    # selected first, so a burst's samples come in the channels' order: each line's slot
    chans = sorted((g[net] - ADC_FIRST_GPIO, net) for net in ("HALL", "LEV_IPROPI", "MUX_OUT"))
    L.append("/* the round robin (from ADC_RR_FIRST, ascending): a burst's samples in this order */")
    L.append("#define ADC_RR_MASK      0x%xu" % sum(1 << c for c, _ in chans))
    L.append("#define ADC_RR_FIRST     %d" % chans[0][0])
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        L.append("#define ADC_SLOT_%-10s %d   /* ADC%d */" % (net, slot, c))
    L.append("")

    L.append("/* ---- the 74HC4051 (S0-S2 on PIN_MUX_S0..S2) ------------------------------ */")
    s0, s1, s2 = g["MUX_S0"], g["MUX_S1"], g["MUX_S2"]
    assert s1 == s0 + 1 and s2 == s0 + 2, "the mux select pins must be adjacent (one masked write)"
    L.append("#define MUX_SEL_SHIFT    %d" % s0)
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    """The SDK's board header names the console UART's and the I2C bus's pins (stdio and
    the SDK's defaults use them): keep them on the pins gen/pins.py gives.  The instances
    stay UART0 and I2C0 (gen/assign.py binds them only to pins those allow)."""
    assert (g["UART_TX"], g["UART_RX"]) in ((0, 1), (12, 13), (16, 17), (28, 29)), "UART0 cannot use these pins"
    assert g["SDA"] % 4 == 0 and g["SCL"] == g["SDA"] + 1, "I2C0 cannot use these pins"
    s = open(BOARD_H).read()
    for name, pin in (("UART_TX_PIN", g["UART_TX"]), ("UART_RX_PIN", g["UART_RX"]),
                      ("I2C_SDA_PIN", g["SDA"]), ("I2C_SCL_PIN", g["SCL"])):
        s, n = re.subn(r"(#define PICO_DEFAULT_%s )\d+" % name, r"\g<1>%d" % pin, s)
        assert n == 1, "no PICO_DEFAULT_%s in %s" % (name, BOARD_H)
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
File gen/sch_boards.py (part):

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            x = q[0] + side * G
            W(q, (x, q[1]))
            S().power(gt, x, q[1], rot=90 if side > 0 else 270)
    # J101's odd pins: the Hall line (on over the top to J102), the bus, grounds
    xh1, yh = p1[1][0] - G, 69.85
    xh2 = p2[1][0] + G
    W(p1[1], (xh1, p1[1][1]), (xh1, yh), (xh2, yh), (xh2, p2[1][1]), p2[1])
    label(xh1 + 2.0, yh, "HALL")
    xg = p1[7][0] - 5.08
    for p in (7, 9, 11, 13, 15):
        W(p1[p], (xg, p1[p][1]))
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    xc0, xc1 = p2[13][0] + 12.7, p2[13][0] + 10.16
    W(o33, (o33[0] - 5.08, o33[1]), (o33[0] - 5.08, yb0), (xc0, yb0), (xc0, p2[13][1]), p2[13])
    W(o34, (o34[0] - G, o34[1]), (o34[0] - G, yb1), (xc1, yb1), (xc1, p2[15][1]), p2[15])
    label(o33[0] + 60.0, yb0, "DOWN0"); label(o33[0] + 60.0, yb1, "DOWN1")
    # 4.8 V: 10 uF at the plug
    xc = 220.98
    tag("tree:c5v"); t, b = vpart("C10U", nref("C"), xc, 140.97, fsize=1.0)
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    W((xa, p[8][1]), (xa + 7.62, p[8][1]), (xa + 7.62, la[1]), la)
    W((xa, p[14][1]), (xa + 10.16, p[14][1]), (xa + 10.16, lb[1]), lb)
    J(xa, p[8][1]); J(xa, p[14][1])
    label(p[8][0] + 1.0, p[8][1], "LEV_B"); label(p[14][0] + 1.0, p[14][1], "LEV_A")
    for q, net in ((p[2], v3), (p[4], v5)):
        W(q, (q[0] + G, q[1])); flag(net, q[0] + G, q[1], rot=90)
    for n in (6, 12):
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    xc = r[0] + 7.62
    W(r, (xc, out[1]), p[1])
    tag("perch:chall"); down("C10N", xc, out[1], net=gp_)
    label(xc + 2.0, out[1], "HALL")
    vcc = u.pin("1")
    yr = vcc[1] - 7.62
    W(vcc, (vcc[0], yr))
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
